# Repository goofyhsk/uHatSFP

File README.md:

# uHatSFP
Re-Interpretation of 'PiHat SFP "encoder"' by PcDwarf - https://hackaday.io/project/21725-pihat-sfp-encoder [^1]  

>This project is a small PCB "piHat" design to interface the I2C bus of SFP and SFP+ modules with a raspberry Pi.

Mine will be recreated (for fun / to learn) with my [uHAT](https://github.com/goofyhsk/uHat) base.  
This should also be compatible with full size Pi  

Note: since there is no EEPROM it can't be called a HAT :)

I intend to include gerbers for various SFP Cage models, with both SMT and TH HAT bases.  
I am also adding a secondary 4P Header for ability to use (i2c) without a RPi

[^1]: Renamed Gerbers for Fab available at https://github.com/xunker/pihat_sfp_encoder_gerbers

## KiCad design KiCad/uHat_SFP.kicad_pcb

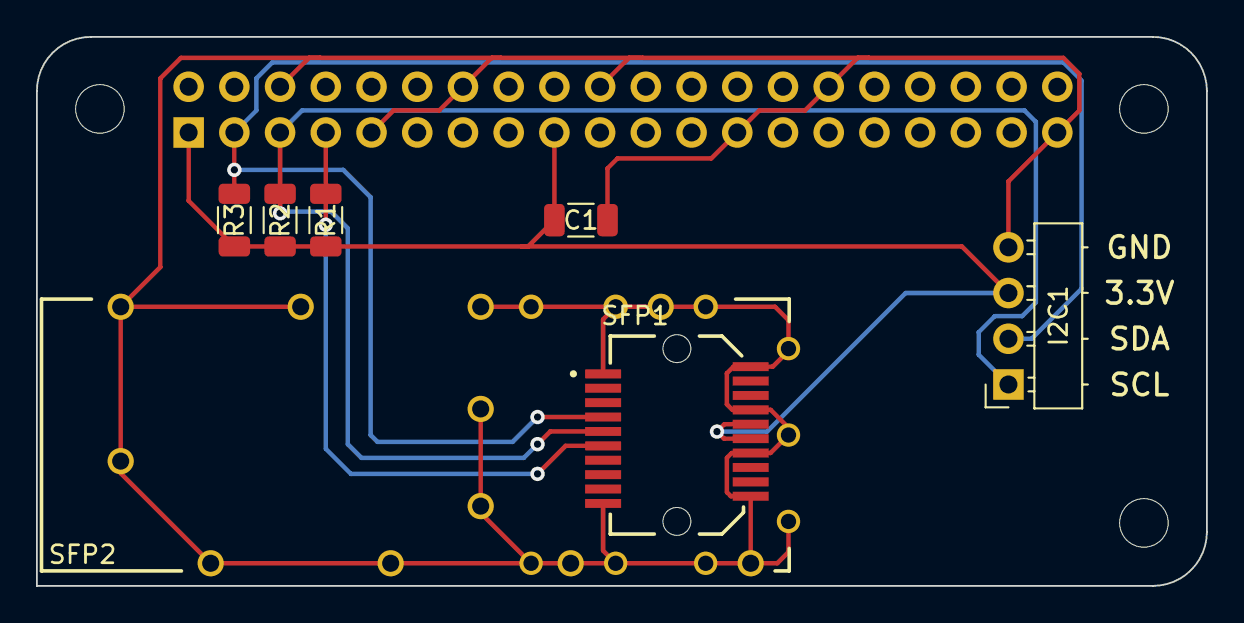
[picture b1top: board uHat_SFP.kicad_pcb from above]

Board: 2 copper layers, 65.0 x 30.5 mm, 11 parts (1 on the bottom side), 5 nets.

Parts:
C1: 100nF; C_1206_3216Metric
GPIO1: GPIO; PinSocket_2x20_P2.54mm_Vertical
H1, H2, H3: MountingHole; MountingHole_2.7mm_M2.5
I2C1: Conn_01x04; PinHeader_1x04_P2.54mm_Horizontal
R1, R2, R3: 10K; R_1206_3216Metric
SFP1: SFP+; SAMTEC_MECT-110-01-M-D-RA1
SFP2: SFPC-SL; SAMTEC_SFPC-SL

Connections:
+3.3V: C1.1, GPIO1.1, GPIO1.17, I2C1.3, R1.1, R2.1, R3.1, SFP1.15 (VccR), SFP1.16 (VccT)
/MOD-DEF0: GPIO1.7, R1.2, SFP1.06 (MOD_DEF0)
/MOD-DEF1: GPIO1.5, I2C1.1, R2.2, SFP1.05 (MOD_DEF1)
/MOD-DEF2: GPIO1.3, I2C1.2, R3.2, SFP1.04 (MOD_DEF2)
GND: C1.2, GPIO1.6, GPIO1.9, GPIO1.14, GPIO1.20, GPIO1.25, GPIO1.30, GPIO1.39, I2C1.4, SFP1.01 (VeeT), SFP1.10 (VeeR), SFP1.11 (VeeT), SFP1.14 (VeeR), SFP1.17 (VeeT), SFP1.20 (VeeR), SFP2.S1 (SHIELD), SFP2.S2 (SHIELD), SFP2.S3 (SHIELD), SFP2.S4 (SHIELD), SFP2.S5 (SHIELD), SFP2.S6 (SHIELD), SFP2.S7 (SHIELD), SFP2.S8 (SHIELD), SFP2.S9 (SHIELD), SFP2.S10 (SHIELD), SFP2.S11 (SHIELD), SFP2.S12 (SHIELD), SFP2.S13 (SHIELD), SFP2.S14 (SHIELD), SFP2.S15 (SHIELD), SFP2.S16 (SHIELD), SFP2.S17 (SHIELD), SFP2.S18 (SHIELD), SFP2.S19 (SHIELD), SFP2.S20 (SHIELD)

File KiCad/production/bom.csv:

Designator,Footprint,Quantity,Value,LCSC Part #
C1,1206,1,100nF,
GPIO1,PinSocket_2x20_P2.54mm_Vertical,1,GPIO,
"H1, H2, H3",MountingHole_2.7mm_M2.5,3,MountingHole,
I2C1,PinHeader_1x04_P2.54mm_Horizontal,1,Conn_01x04,
R1,1206,1,10K,
R2,1206,1,10K,
R3,1206,1,10K,
SFP1,SAMTEC_MECT-110-01-M-D-RA1,1,SFP+,
SFP2,SAMTEC_SFPC-SL,1,SFPC-SL,

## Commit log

2023-02-07 Added PCDwarf Pictures
2023-02-07 Update Gerber Pic with Top / Bottom
2023-02-07 Filename
2023-02-07 Formatting
2023-02-07 Markdown
2023-03-07 Update README.md
    HAT but not HAT
2023-03-14 Possibly Working Project
